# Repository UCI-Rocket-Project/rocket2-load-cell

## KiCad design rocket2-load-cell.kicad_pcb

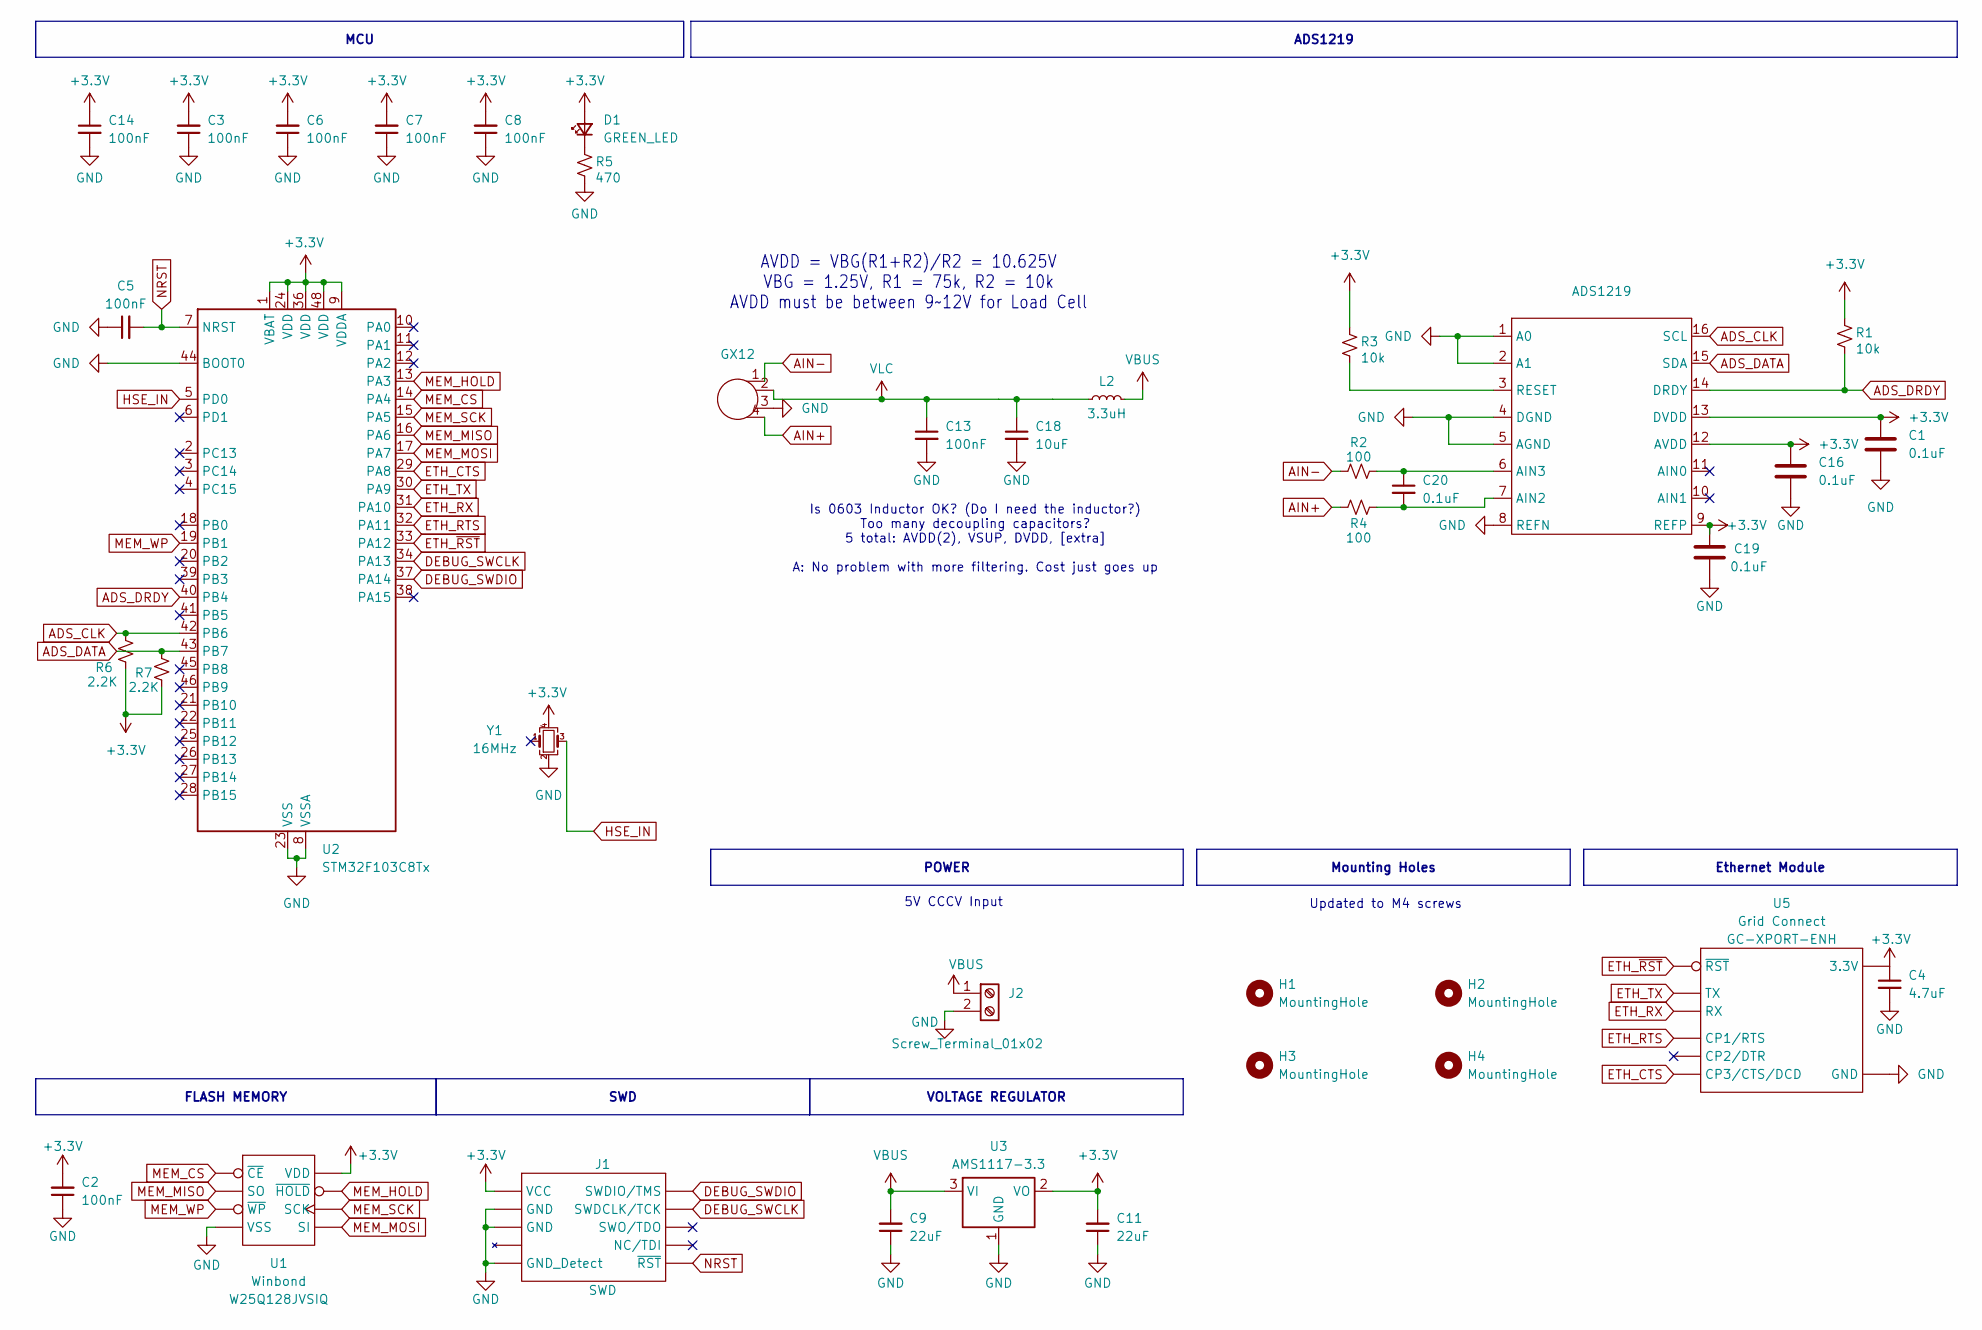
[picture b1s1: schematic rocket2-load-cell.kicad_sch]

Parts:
ADS1219: TSSOP-16_4.4x5mm_P0.65mm
C1, C20: 0.1uF; C_0603_1608Metric
C2, C3, C5, C6, C7, C8, C13, C14: 100nF; C_0603_1608Metric
C4: 4.7uF; C_0603_1608Metric; Part # Generic 4.7uF 6.3V X7R 0603 MLCC
C9, C11: 22uF; C_0603_1608Metric
C16, C19: 0.1uF; C_0603_1608Metric_Pad1.08x0.95mm_HandSolder
C18: 10uF; C_0603_1608Metric
D1: GREEN_LED; LED_0603_1608Metric
GX12: gx12
H1, H2, H3, H4: MountingHole; MountingHole_4.3mm_M4
J1: SWD; PinHeader_2x05_P1.27mm_Vertical_SMD; Part # Generic 2x05 P1.27mm Vertical Pin Heade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
J2: Screw_Terminal_01x02; TerminalBlock_Phoenix_MKDS-1,5-2-5.08_1x02_P5.08mm_Horizont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
L2: 3.3uH; L_0603_1608Metric
R1, R3: 10k; R_0603_1608Metric
R2, R4: 100; R_0603_1608Metric
R5: 470; R_0603_1608Metric
R6, R7: 2.2K; R_0603_1608Metric
U1: SOIC-8W_5.3x5.3mm_P1.27mm; Part # W25Q128JVSIQ
U2: STM32F103C8Tx; LQFP-48_7x7mm_P0.5mm
U3: AMS1117-3.3; SOT-223-3_TabPin2
U5: GC-XPORT; Part # GC-XPORT-ENH
Y1: 16MHz; Crystal_SMD_2520-4Pin_2.5x2.0mm; Part # ECS-1633-160-BN-TR

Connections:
+3.3V: ADS1219.9 (REFP), ADS1219.12 (AVDD), ADS1219.13 (DVDD), C1.1, C2.2, C3.2, C4.1, C6.2, C7.2, C8.2, C11.2, C14.1, C16.1, C19.1, D1.2 (A), J1.1 (VCC), R1.2, R3.2, R6.1, R7.1, U1.8 (VDD), U2.1 (VBAT), U2.9 (VDDA), U2.24 (VDD), U2.36 (VDD), U2.48 (VDD), U3.2 (VO), U5.2 (3.3V), Y1.4
ADS_CLK: ADS1219.16 (SCL), R6.2, U2.42 (PB6)
ADS_DATA: ADS1219.15 (SDA), R7.2, U2.43 (PB7)
ADS_DRDY: ADS1219.14 (DRDY), R1.1, U2.40 (PB4)
AIN+: GX12.4, R4.1
AIN-: GX12.1, R2.1
DEBUG_SWCLK: J1.4 (SWDCLK/TCK), U2.34 (PA13)
DEBUG_SWDIO: J1.2 (SWDIO/TMS), U2.37 (PA14)
ETH_CTS: U2.29 (PA8), U5.8 (CP3/CTS/DCD)
ETH_RTS: U2.32 (PA11), U5.6 (CP1/RTS)
ETH_RX: U2.31 (PA10), U5.5 (RX)
ETH_TX: U2.30 (PA9), U5.4 (TX)
ETH_~RST: U2.33 (PA12), U5.3 (~RST)
GND: ADS1219.1 (A0), ADS1219.2 (A1), ADS1219.4 (DGND), ADS1219.5 (AGND), ADS1219.8 (REFN), C1.2, C2.1, C3.1, C4.2, C5.1, C6.1, C7.1, C8.1, C9.1, C11.1, C13.2, C14.2, C16.2, C18.2, C19.2, GX12.3, J1.3 (GND), J1.5 (GND), J1.9 (GND_Detect), J2.2, R5.1, U1.4 (VSS), U2.8 (VSSA), U2.23 (VSS), U2.35 (VSS), U2.44 (BOOT0), U2.47 (VSS), U3.1 (GND), U5.1 (GND), Y1.2
HSE_IN: U2.5 (PD0), Y1.3
MEM_CS: U1.1 (~CE), U2.14 (PA4)
MEM_HOLD: U1.7 (~HOLD), U2.13 (PA3)
MEM_MISO: U1.2 (SO), U2.16 (PA6)
MEM_MOSI: U1.5 (SI), U2.17 (PA7)
MEM_SCK: U1.6 (SCK), U2.15 (PA5)
MEM_WP: U1.3 (~WP), U2.19 (PB1)
NRST: C5.2, J1.10 (~RST), U2.7 (NRST)
unnamed: ADS1219.7 (AIN2), C20.2, R4.2
unnamed: ADS1219.6 (AIN3), C20.1, R2.2
unnamed: ADS1219.3 (RESET), R3.1
unnamed: D1.1 (K), R5.2
VBUS: C9.2, J2.1, L2.2, U3.3 (VI)
VLC: C13.1, C18.1, GX12.2, L2.1

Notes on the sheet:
FLASH MEMORY
POWER
VOLTAGE REGULATOR
Mounting Holes
SWD
Ethernet Module
ADS1219
MCU
Updated to M4 screws
AVDD = VBG(R1+R2)/R2 = 10.625V VBG = 1.25V, R1 = 75k, R2 = 10k AVDD must be between 9~12V for Load Cell
5V CCCV Input
Is 0603 Inductor OK? (Do I need the inductor?) Too many decoupling capacitors? 5 total: AVDD(2), VSUP, DVDD, [extra] A: No problem with more filtering. Cost just goes up

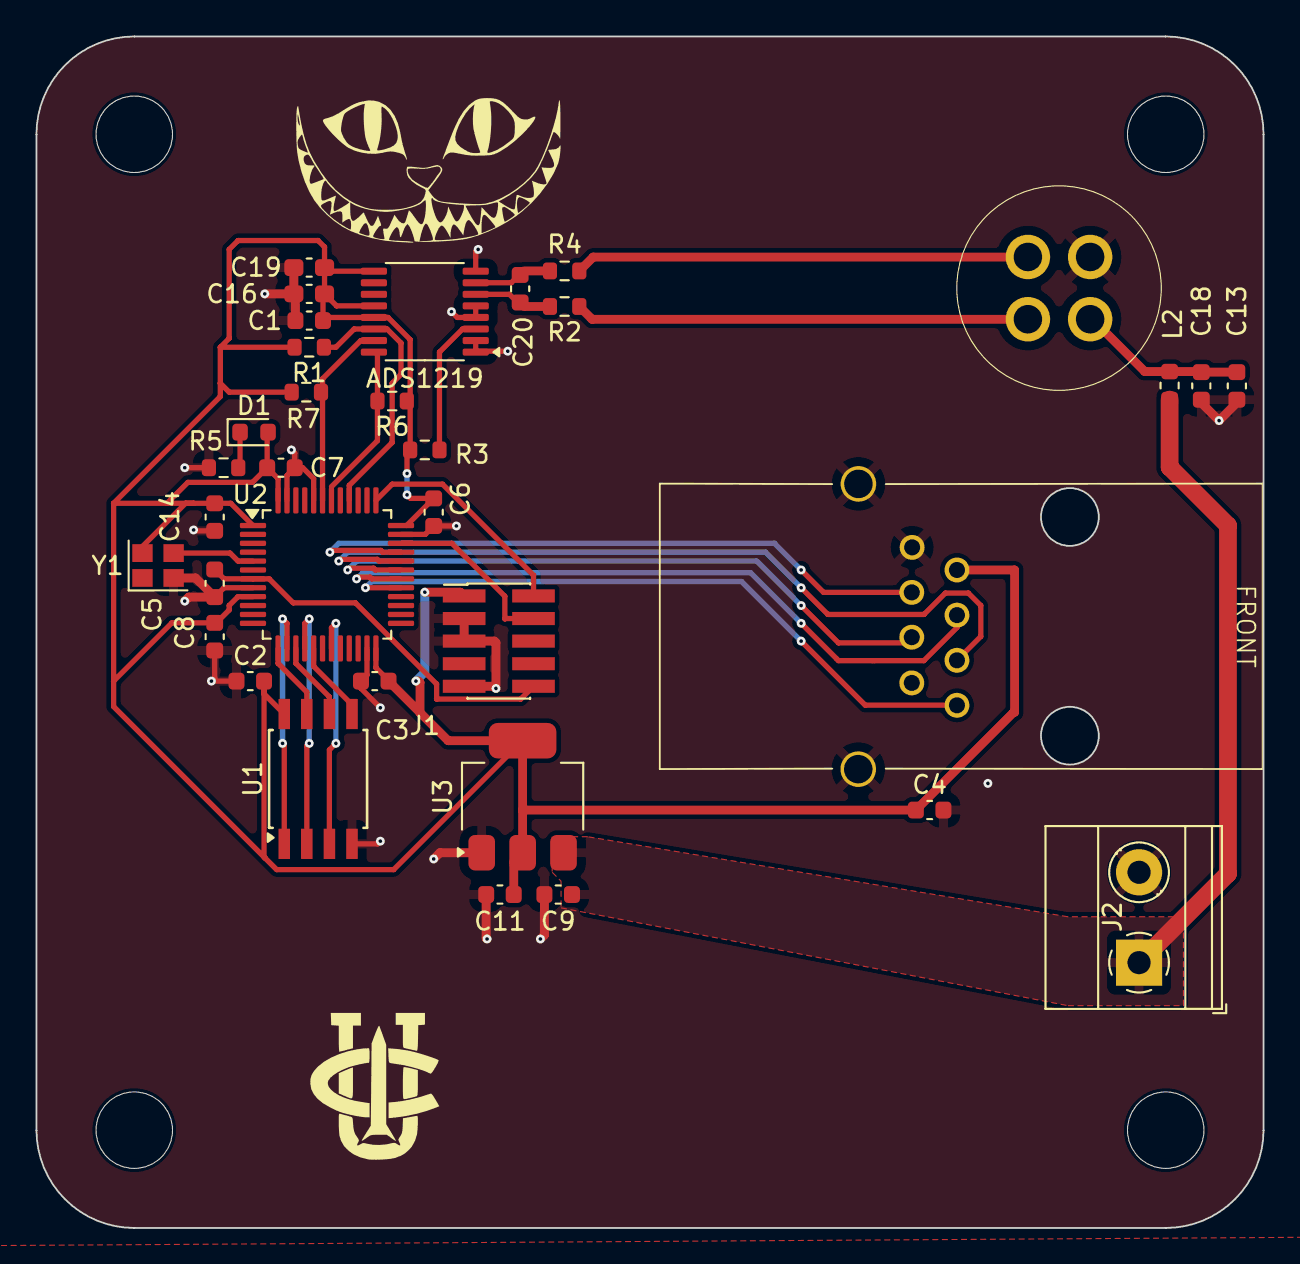
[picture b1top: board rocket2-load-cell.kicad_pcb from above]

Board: 2 copper layers, 69.0 x 67.0 mm, 38 parts (0 on the bottom side), 28 nets.

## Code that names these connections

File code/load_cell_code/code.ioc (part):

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Mcu.Name=STM32F103C(8-B)Tx
Mcu.Package=LQFP48
Mcu.UserName=STM32F103C8Tx
PA10.Mode=Asynchronous
PA10.Signal=USART1_RX
PA12.Signal=GPIO_Output
PA13.Mode=Serial_Wire
PA13.Signal=SYS_JTMS-SWDIO
PA14.Mode=Serial_Wire
PA14.Signal=SYS_JTCK-SWCLK
PA3.Signal=GPIO_Output
PA4.Mode=NSS_Signal_Hard_Output
PA4.Signal=SPI1_NSS
PA5.Mode=Full_Duplex_Master
PA5.Signal=SPI1_SCK
PA6.Mode=Full_Duplex_Master
PA6.Signal=SPI1_MISO
PA7.Mode=Full_Duplex_Master
PA7.Signal=SPI1_MOSI
PA9.Mode=Asynchronous
PA9.Signal=USART1_TX
PB1.Signal=GPIO_Output
PB4.Signal=GPIO_Input
PB6.Mode=I2C
PB6.Signal=I2C1_SCL
PB7.Mode=I2C
PB7.Signal=I2C1_SDA
RCC.HSEDivPLL=RCC_HSE_PREDIV_DIV2
RCC.HSE_VALUE=16000000
RCC.SYSCLKFreq_VALUE=36000000
RCC.SYSCLKSource=RCC_SYSCLKSOURCE_PLLCLK
board=custom

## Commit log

2024-09-28 Imported UCIRP KiCad template files
2024-09-28 .gitignore
2024-10-07 David's Schematic
2024-10-07 HSE Crystal (16MHz) and Adjusted AVDD (10.625V)
2024-10-08 Changed to small components. Added +5V power supply
2024-10-08 Tidied up schematic, added comments for Daniel
2024-10-08 Resolved comments. Need new amplifier for faster sampling.
2024-10-08 Load cell E+ +3.3 -> +5V
2024-11-21 added working arduino code as well as testread.py(nonop)
2024-11-22 updated code complete with scale zero on client connection
2024-11-24 added graphing for matplot lib
2024-12-01 added final scaling changed and print debugging
2024-12-03 finished routing file(submit for review)
2024-12-03 submitting for review
2024-12-03 Revert "submitting for review"
    This reverts commit 1e17fc2b929a1369e5cebb95b8d17141503d9833.
    accidentaly deleted schematic...
2024-12-03 Revert "finished routing file(submit for review)"
    This reverts commit a7b270876cc0567c9db231a326dac314d918e378.
2024-12-03 fixed back up issue
2024-12-03 added images and made it coooooooooooooollllllllllllllllllllllllllllllllllllllllllllllllllll
2024-12-04 added cool images to loadcell silk screen
2025-01-07 added ethernet module as well as fixing some wireing issues
2025-01-07 fixed important erc errors
2025-01-08 okay final final change this time, also added fabrication files
2025-01-09 made it so that all vias are connected, should be good for fabrication, no design errors now
2025-01-15 added gx12 connector and fixed varioius other design problems
2025-01-15 added cad models to board
2025-01-15 changed via locations
2025-01-15 cleaned up vias once again removed redundant tracks
2025-01-15 moved gx12 futher from ethernet
2025-01-27 changed back to 5v and removed 12 volt reg
2025-04-24 added stm32 prroject
2025-05-16 added code and stab
2025-05-17 changed code
2025-05-17 added python notebook
